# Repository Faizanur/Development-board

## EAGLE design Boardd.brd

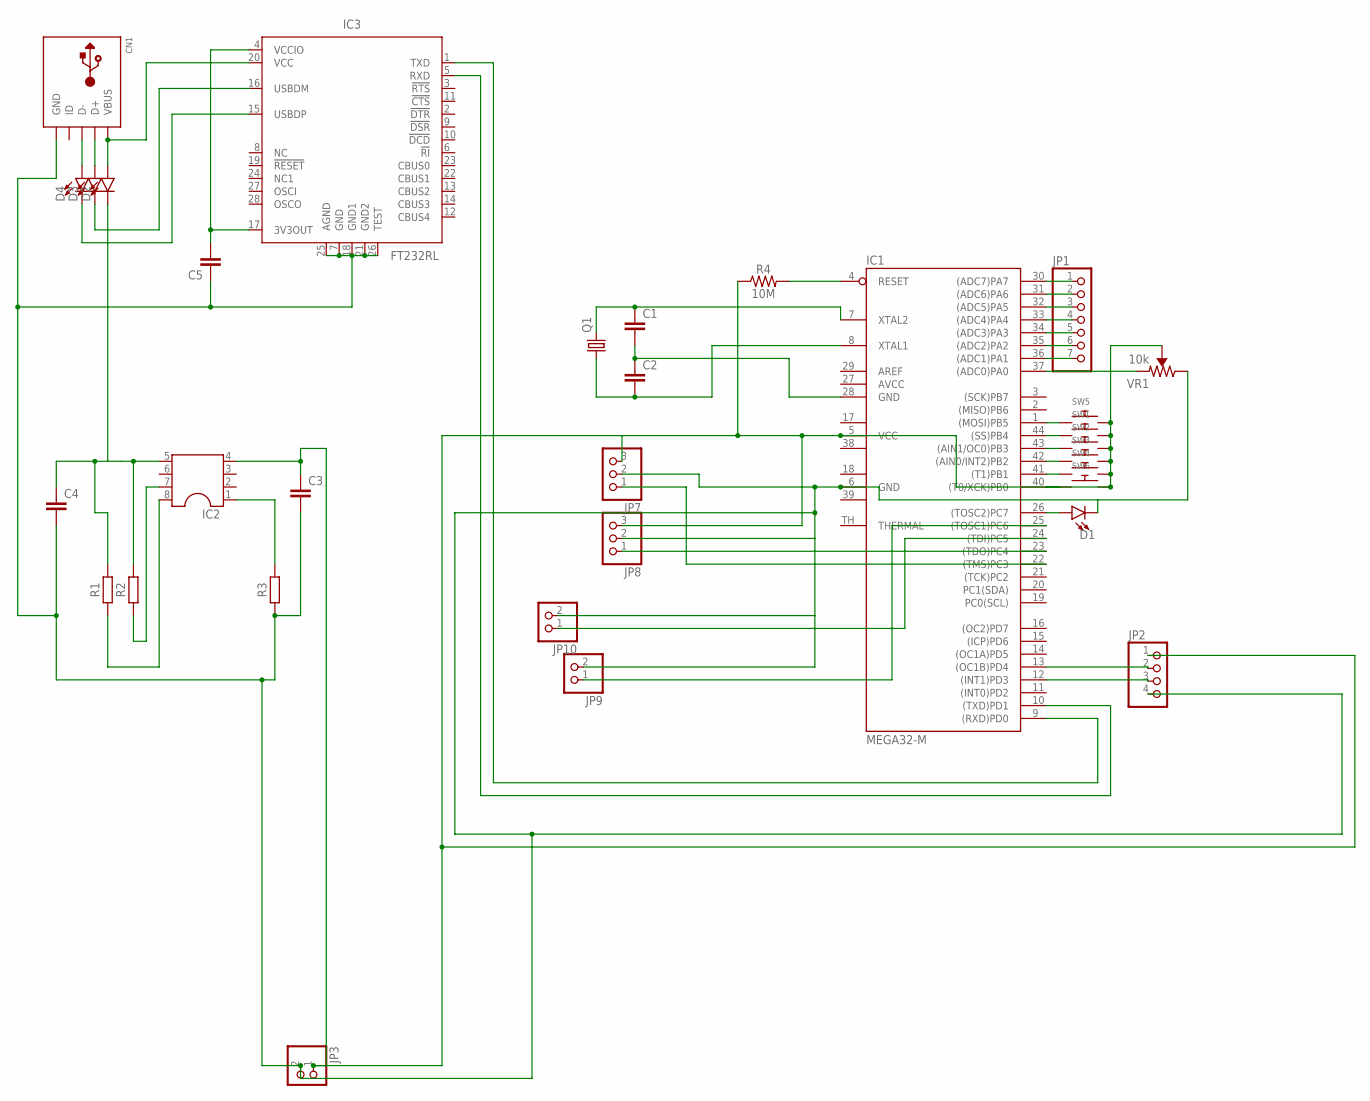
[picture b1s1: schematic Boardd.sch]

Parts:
C1, C2, C5: C2,5-3; C2.5-3
C3, C4: C2.5/2; C2.5-2
CN1: USBMINIB; USB-MINIB
D1, D2, D3, D4: LED0603; LED-0603
IC1: MEGA32-M; MLF44-TH
IC2: DIL8; DIL08
IC3: FT232RL; SSOP28
JP1: PINHD-1X7; 1X07
JP2: PINHD-1X4; 1X04
JP3, JP9, JP10: PINHD-1X2; 1X02
JP7, JP8: PINHD-1X3; 1X03
Q1: CRYSTALHC49S; HC49/S
R1, R2, R3: R_CHIP-0603(1608-METRIC); RESC1608X60
R4: 10M; 0603
SW1, SW2, SW3, SW4, SW5, SW6: SWITCH_PUSHBUTTONSOFTTOUCHSMD_SJ; PUSHBUTTON_SMD_SJ
VR1: 10k; TRIMPOT-SMD-3MM-CLOSED

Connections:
AVCC: IC1.27 (AVCC)
GND1: IC1.18 (GND1)
GND2: IC1.39 (GND2)
unnamed: IC1.1 ((MOSI)PB5), SW5.P$1
unnamed: IC1.44 ((SS)PB4), SW1.P$1
unnamed: IC1.43 ((AIN1/OC0)PB3), SW2.P$1
unnamed: IC1.42 ((AIN0/INT2)PB2), SW3.P$1
unnamed: D1.A, IC1.26 ((TOSC2)PC7)
unnamed: IC1.41 ((T1)PB1), SW4.P$1
unnamed: IC1.40 ((T0/XCK)PB0), SW6.P$1
unnamed: C1.2, C2.1, IC1.28 (GND)
unnamed: C1.1, IC1.7 (XTAL2), Q1.2
unnamed: C2.2, IC1.8 (XTAL1), Q1.1
unnamed: IC1.37 ((ADC0)PA0), VR1.1 (CCW)
unnamed: IC1.30 ((ADC7)PA7), JP1.1
unnamed: IC1.31 ((ADC6)PA6), JP1.2
unnamed: IC1.32 ((ADC5)PA5), JP1.3
unnamed: IC1.13 ((OC1B)PD4), JP2.2
unnamed: IC1.12 ((INT1)PD3), JP2.3
unnamed: IC1.33 ((ADC4)PA4), JP1.4
unnamed: IC1.34 ((ADC3)PA3), JP1.5
unnamed: IC1.35 ((ADC2)PA2), JP1.6
unnamed: IC1.36 ((ADC1)PA1), JP1.7
unnamed: C3.1, IC1.5 (VCC), IC2.4, JP2.1, JP3.1, JP7.3, JP8.3, R4.1, SW1.P$2, SW2.P$2, SW3.P$2, SW4.P$2, SW5.P$2, SW6.P$2, VR1.2 (WIPER)
unnamed: CN1.VBUS, D2.A, IC3.20 (VCC)
unnamed: IC1.25 ((TOSC1)PC6), JP9.1
unnamed: IC1.24 ((TDI)PC5), JP10.1
unnamed: IC1.4 (RESET), R4.2
unnamed: CN1.D+, D3.A
unnamed: CN1.D-, D4.A
unnamed: D3.C, IC3.16 (USBDM)
unnamed: D4.C, IC3.15 (USBDP)
unnamed: C3.2, C4.2, C5.1, CN1.GND, D1.C, IC1.6 (GND), IC3.7 (GND), IC3.18 (GND1), IC3.21 (GND2), IC3.25 (AGND), IC3.26 (TEST), JP2.4, JP3.2, JP7.2, JP8.2, JP9.2, JP10.2, R3.1, VR1.3 (CW)
unnamed: IC1.10 ((TXD)PD1), IC3.5 (RXD)
unnamed: IC1.9 ((RXD)PD0), IC3.1 (TXD)
unnamed: C5.2, IC3.4 (VCCIO), IC3.17 (3V3OUT)
unnamed: IC1.23 ((TDO)PC4), JP8.1
unnamed: IC1.22 ((TMS)PC3), JP7.1
unnamed: IC2.1, R3.2
unnamed: IC2.8, R1.1
unnamed: IC2.7, R2.1
unnamed: C4.1, D2.C, IC2.5, R1.2, R2.2
VCC1: IC1.17 (VCC1)
VCC2: IC1.38 (VCC2)

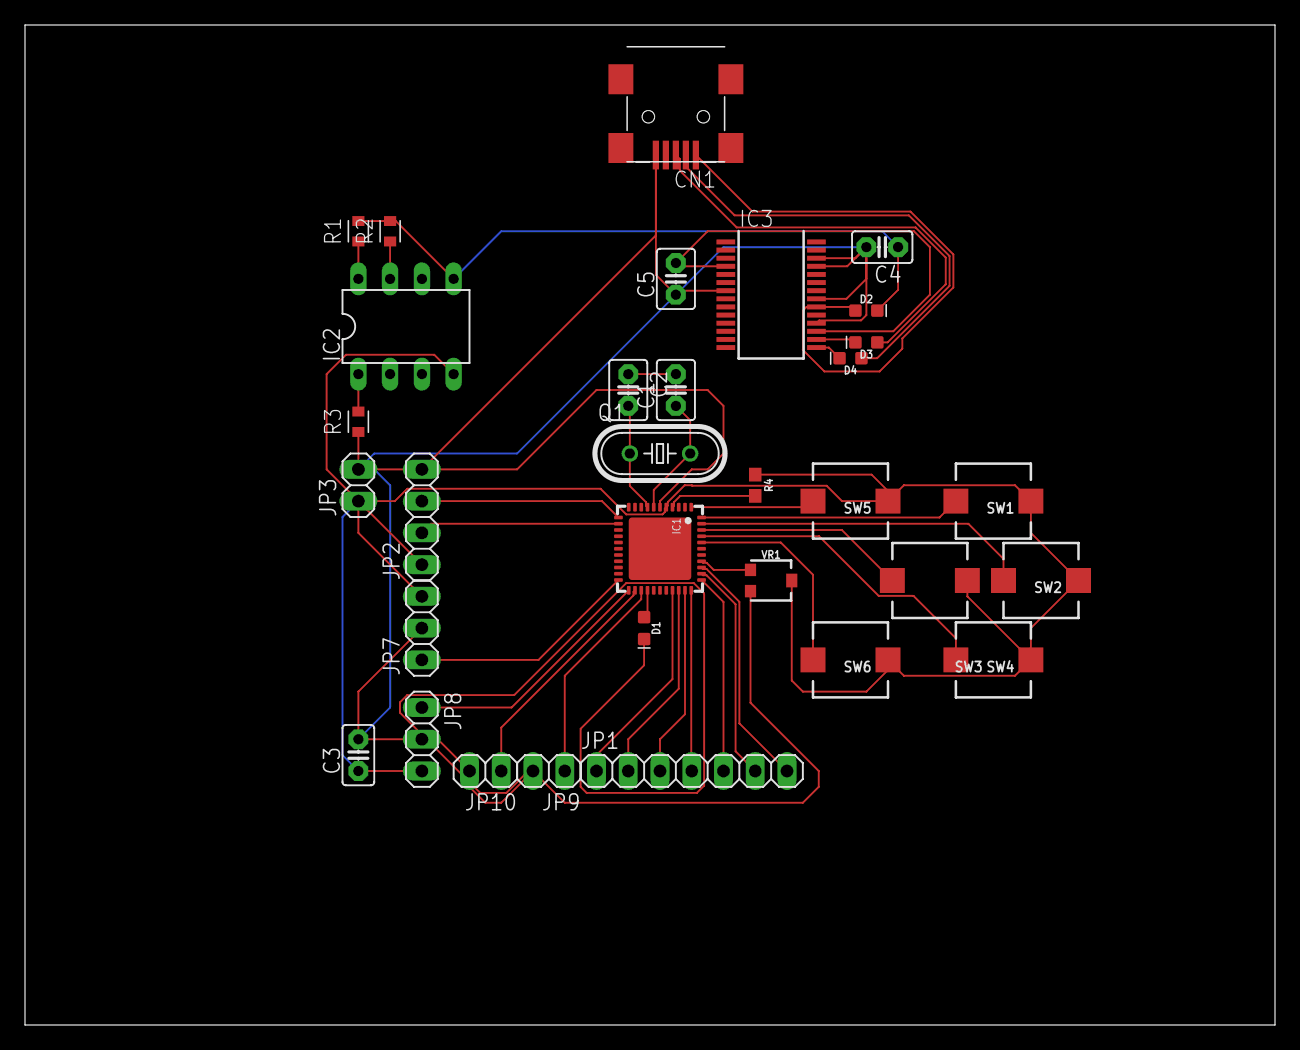
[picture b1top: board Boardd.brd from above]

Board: 2 copper layers, 100.0 x 80.0 mm, 32 parts (0 on the bottom side), 39 nets.

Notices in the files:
parts and their libraries:
SparkFun-LED: Licensing: Creative Commons ShareAlike 4.0 International - https://creativecommons.org/licenses/by-sa/4.0
